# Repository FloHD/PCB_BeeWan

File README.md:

# PCB_BeeWan

Vous pouvez mettre vos remarques ici. Merci.

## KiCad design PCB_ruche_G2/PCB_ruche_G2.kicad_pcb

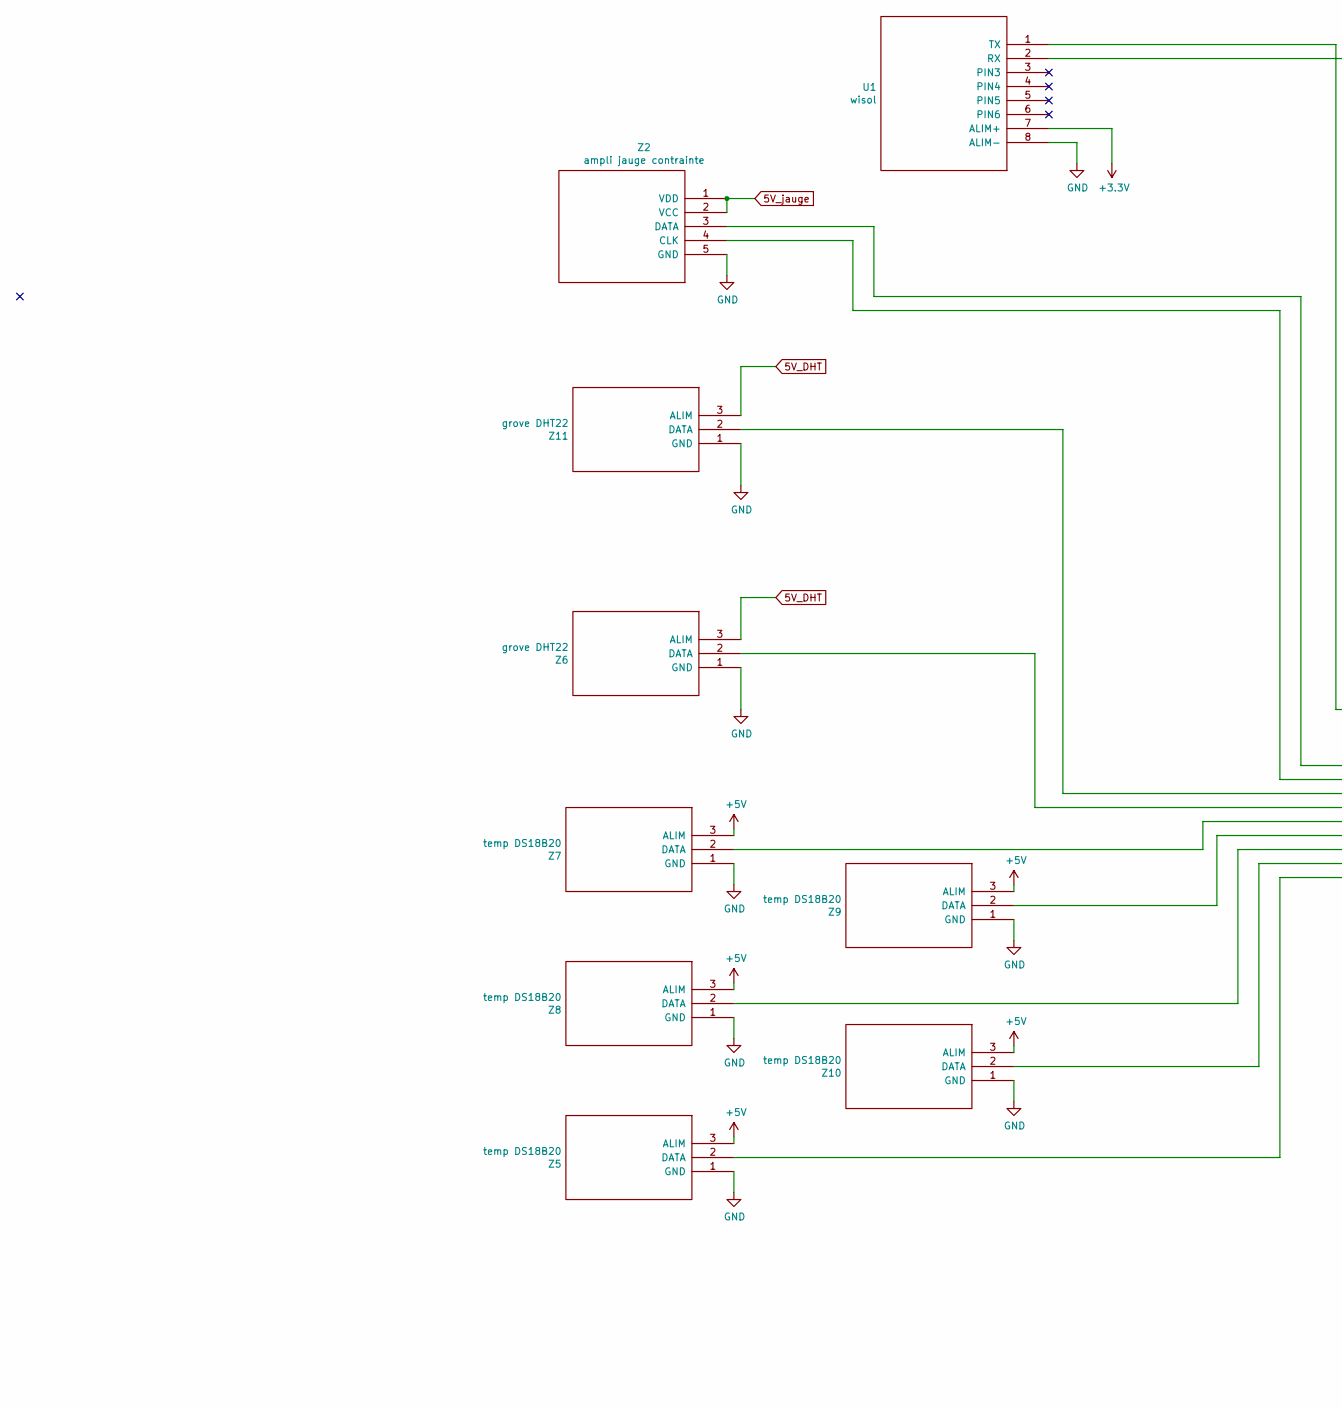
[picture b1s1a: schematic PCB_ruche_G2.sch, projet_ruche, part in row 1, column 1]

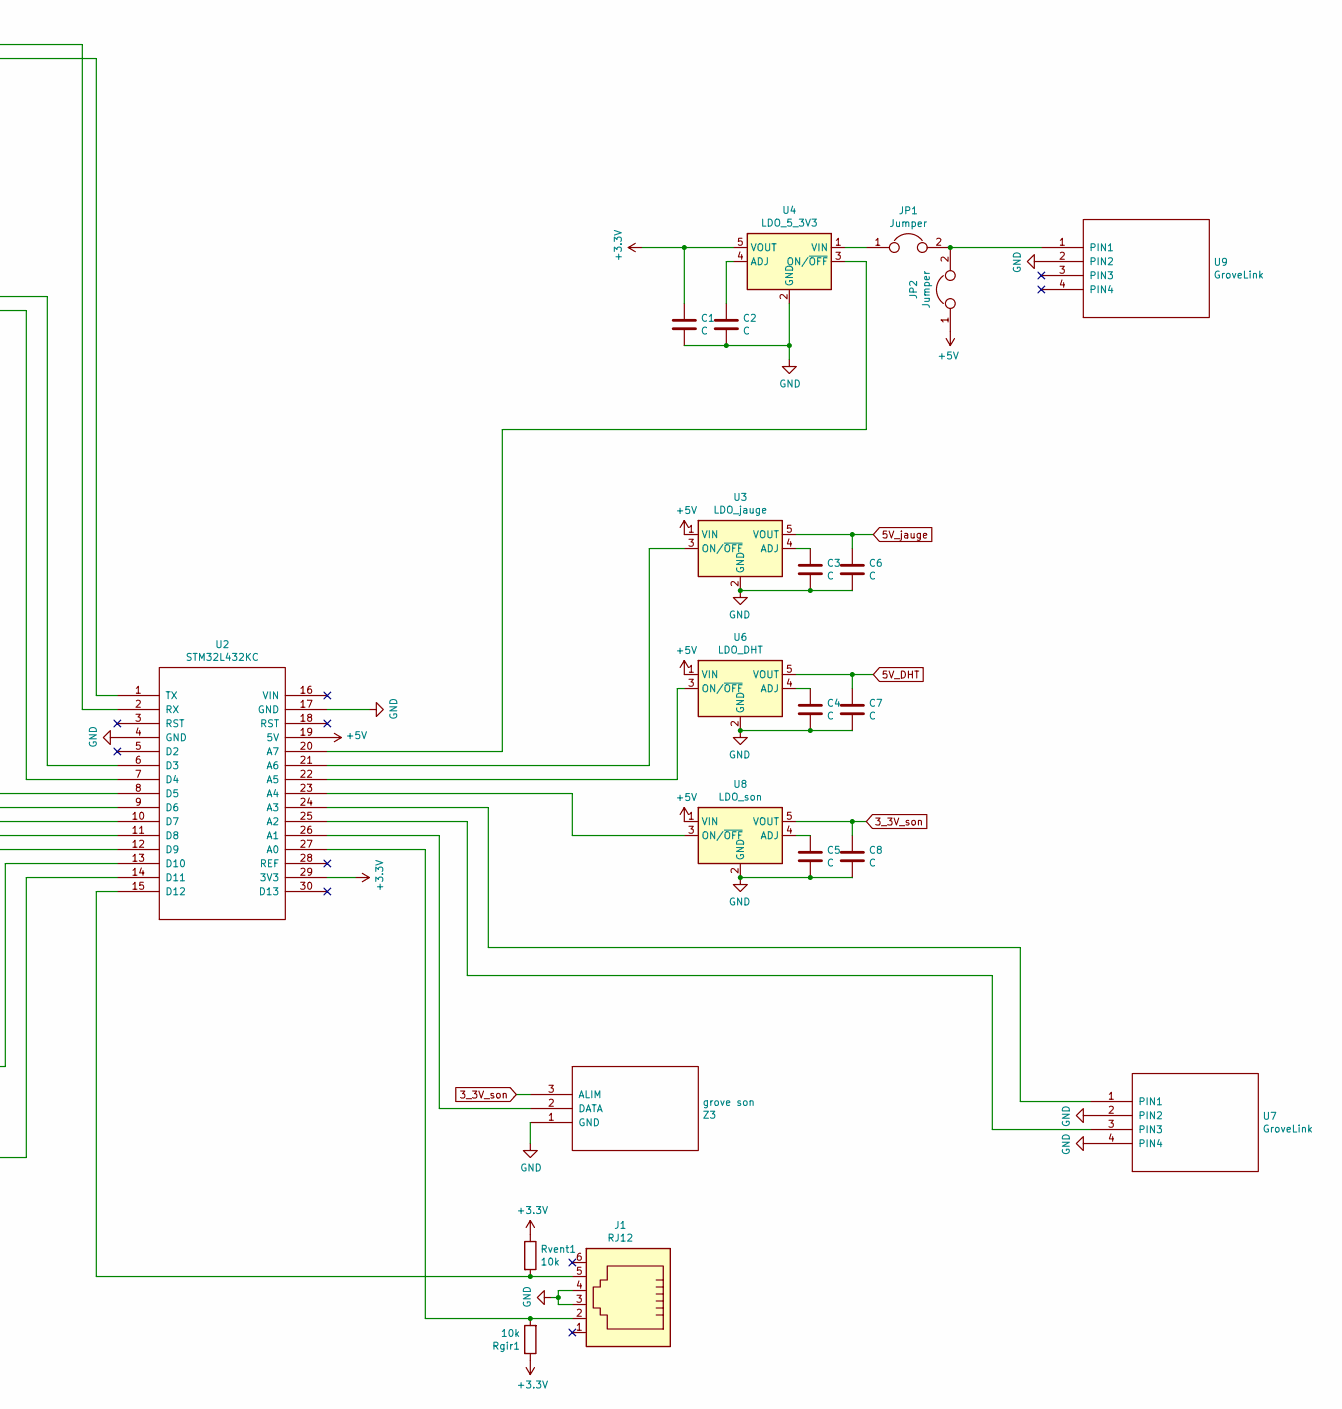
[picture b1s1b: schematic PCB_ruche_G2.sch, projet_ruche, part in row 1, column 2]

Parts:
C1, C2, C3, C4, C5, C6, C7, C8: C; CP_Axial_L10.0mm_D4.5mm_P15.00mm_Horizontal
J1: RJ12; RJ12_Amphenol_54601
JP1, JP2: Jumper; SolderJumper-2_P1.3mm_Bridged2Bar_Pad1.0x1.5mm
Rgir1: 10k; R_Axial_DIN0309_L9.0mm_D3.2mm_P15.24mm_Horizontal
Rvent1: 10k; R_Axial_DIN0309_L9.0mm_D3.2mm_P15.24mm_Horizontal
U1: wisol
U2: STM32L432KC
U3: LDO_jauge; SOT-23-5
U4: LDO_5_3V3; SOT-23-5
U6: LDO_DHT; SOT-23-5
U7, U9: GroveLink
U8: LDO_son; SOT-23-5
Z2: ampli jauge contrainte; ampli_jauge_contrainte
Z3: grove son; temp_hum
Z5, Z7, Z8, Z9, Z10: temp DS18B20; temp_hum
Z6, Z11: grove DHT22; temp_hum

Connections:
3_3V_son: C8.1, U8.5 (VOUT), Z3.3 (ALIM)
5V_DHT: C7.1, U6.5 (VOUT), Z6.3 (ALIM), Z11.3 (ALIM)
5V_jauge: C6.1, U3.5 (VOUT), Z2.1 (VDD), Z2.2 (VCC)
+3V3: C1.1, Rgir1.1, Rvent1.1, U1.7 (ALIM+), U2.29 (3V3), U4.5 (VOUT)
+5V: JP2.1, U2.19 (5V), U3.1 (VIN), U6.1 (VIN), U8.1 (VIN), Z5.3 (ALIM), Z7.3 (ALIM), Z8.3 (ALIM), Z9.3 (ALIM), Z10.3 (ALIM)
GND: C1.2, C2.2, C3.2, C4.2, C5.2, C6.2, C7.2, C8.2, J1.3, J1.4, U1.8 (ALIM-), U2.4 (GND), U2.17 (GND), U3.2 (GND), U4.2 (GND), U6.2 (GND), U7.2 (PIN2), U7.4 (PIN4), U8.2 (GND), U9.2 (PIN2), Z2.5 (GND), Z3.1 (GND), Z5.1 (GND), Z6.1 (GND), Z7.1 (GND), Z8.1 (GND), Z9.1 (GND), Z10.1 (GND), Z11.1 (GND)
unnamed: C2.1, U4.4 (ADJ)
unnamed: C3.1, U3.4 (ADJ)
unnamed: C4.1, U6.4 (ADJ)
unnamed: C5.1, U8.4 (ADJ)
unnamed: J1.2, Rgir1.2, U2.27 (A0)
unnamed: J1.5, Rvent1.2, U2.15 (D12)
unnamed: JP1.1, U4.1 (VIN)
unnamed: JP1.2, JP2.2, U9.1 (PIN1)
unnamed: U1.1 (TX), U2.2 (RX)
unnamed: U1.2 (RX), U2.1 (TX)
unnamed: U2.6 (D3), Z2.3 (DATA)
unnamed: U2.7 (D4), Z2.4 (CLK)
unnamed: U2.8 (D5), Z11.2 (DATA)
unnamed: U2.9 (D6), Z6.2 (DATA)
unnamed: U2.10 (D7), Z7.2 (DATA)
unnamed: U2.11 (D8), Z9.2 (DATA)
unnamed: U2.12 (D9), Z8.2 (DATA)
unnamed: U2.13 (D10), Z10.2 (DATA)
unnamed: U2.14 (D11), Z5.2 (DATA)
unnamed: U2.20 (A7), U4.3 (ON/~OFF)
unnamed: U2.21 (A6), U3.3 (ON/~OFF)
unnamed: U2.22 (A5), U6.3 (ON/~OFF)
unnamed: U2.23 (A4), U8.3 (ON/~OFF)
unnamed: U2.24 (A3), U7.1 (PIN1)
unnamed: U2.25 (A2), U7.3 (PIN3)
unnamed: U2.26 (A1), Z3.2 (DATA)

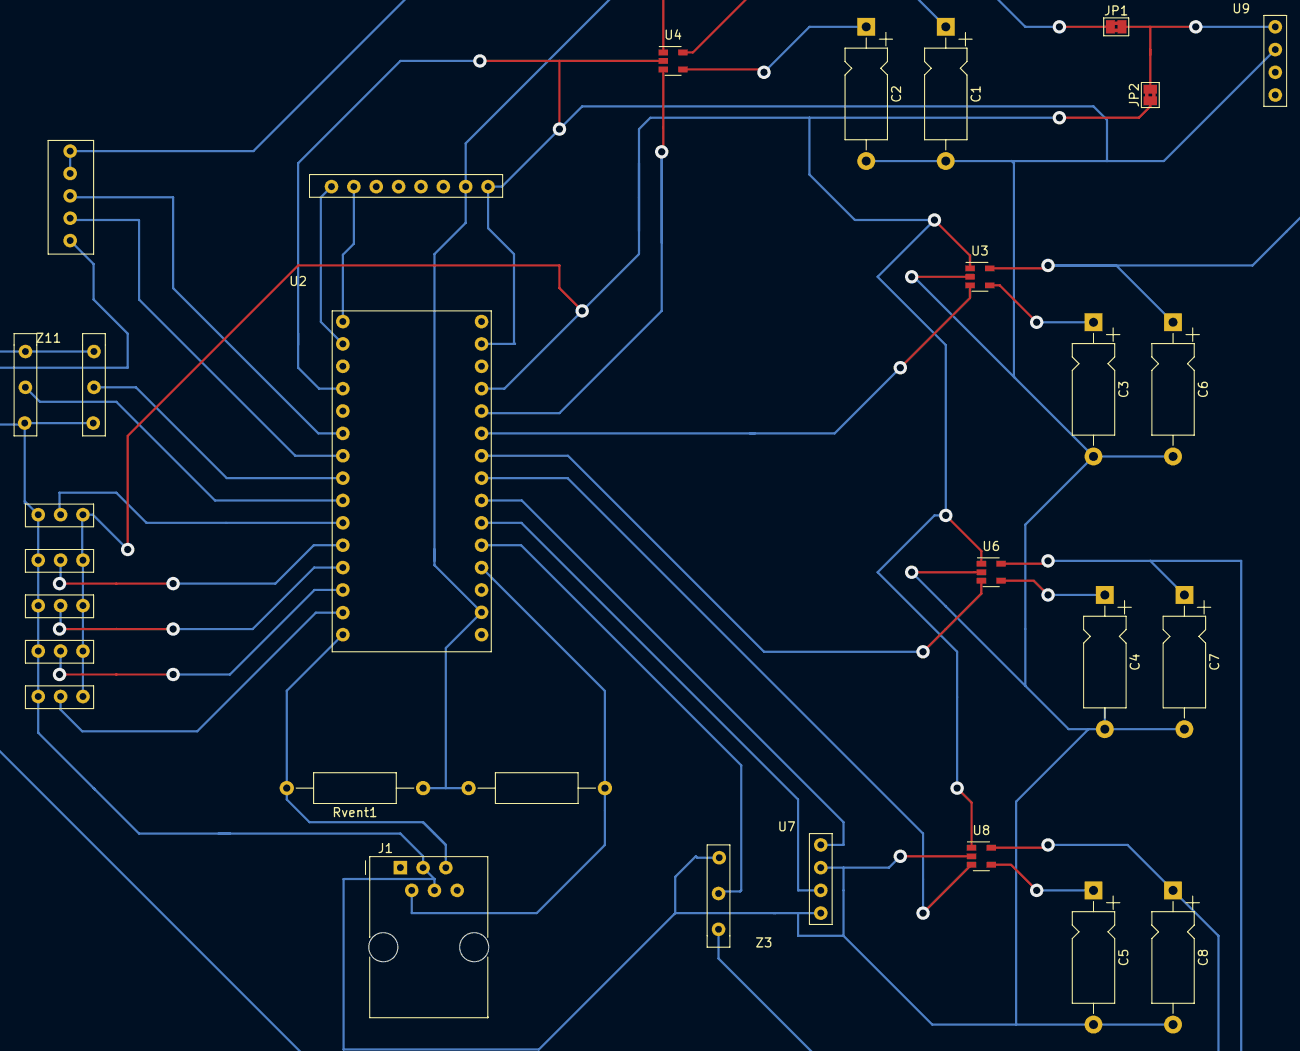
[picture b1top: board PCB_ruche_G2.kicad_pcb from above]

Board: 2 copper layers, 30 parts (0 on the bottom side), 32 nets.
